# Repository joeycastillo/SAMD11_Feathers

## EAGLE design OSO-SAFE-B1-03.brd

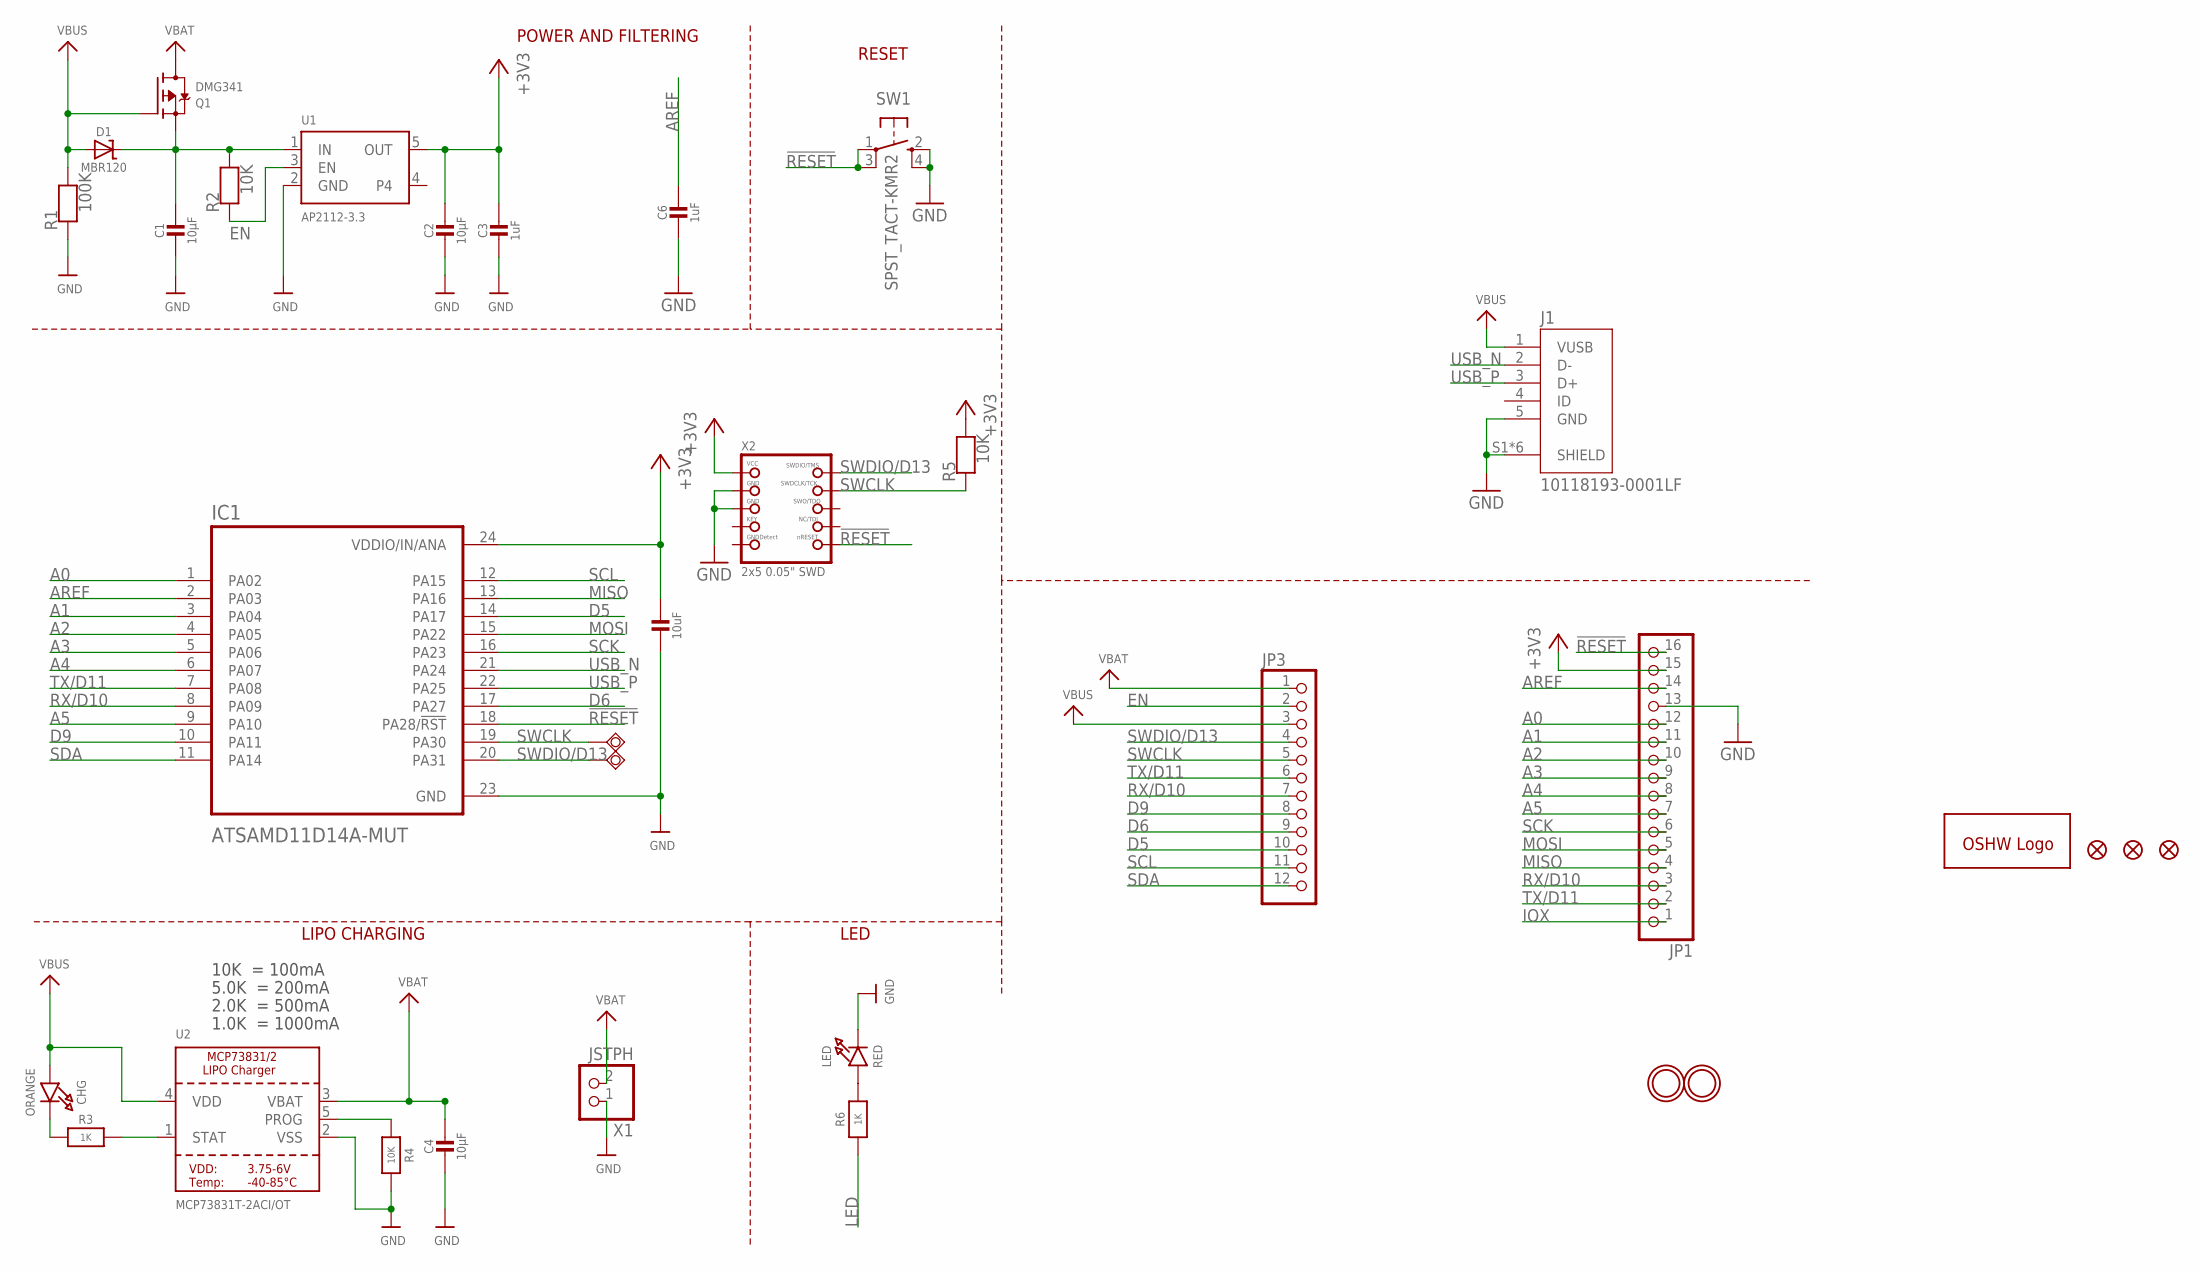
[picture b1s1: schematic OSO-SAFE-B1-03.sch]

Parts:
C1, C2, C4: 10µF; 0805-NO
C3, C6: 1uF; 0805-NO
C5: 10uF; 0805-NO
CHG: ORANGE; CHIPLED_0805_NOOUTLINE
D1: MBR120; SOD-123
FID1, FID3, FID4: FIDUCIAL_1MM
GOLD_ORB_SM1: OSHWLOGOLOGO5MM; OSHW_5MM
IC1: ATSAMD11D14A-MUT; QFN50P400X400X90-25N
J1: 10118193-0001LF; FCI_10118193-0001LF
JP1: HEADER-1X16_MIN; 1X16_ROUND_MIN
JP3: HEADER-1X12_MIN; 1X12_ROUND_MIN
LED: RED; CHIPLED_0805_NOOUTLINE
Q1: DMG341; SOT23-R
R1: 100K; 0805-NO
R2, R4, R5: 10K; 0805-NO
R3, R6: 1K; 0805-NO
SW1: SPST_TACT-KMR2; KMR2
SWCLK: TPSQTP20R; TP20R
SWDIO: TPSQTP20R; TP20R
U1: AP2112-3.3; SOT23-5
U2: MCP73831T-2ACI/OT; SOT23-5
U$31, U$32: MOUNTINGHOLE2.5; MOUNTINGHOLE_2.5_PLATED
X1: JSTPH; JSTPH2
X2: 2x5 0.05" SWD; 2X05_1.27MM_BOX_POSTS

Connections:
!RESET: IC1.18 (PA28/!RST), JP1.16, SW1.1, SW1.3 (P1), X2.10 (NRESET)
+3V3: C2.1, C3.1, C5.1, IC1.24 (VDDIO/IN/ANA), JP1.15, R5.2, U1.5 (OUT), X2.1 (VCC)
A0: IC1.1 (PA02), JP1.12
A1: IC1.3 (PA04), JP1.11
A2: IC1.4 (PA05), JP1.10
A3: IC1.5 (PA06), JP1.9
A4: IC1.6 (PA07), JP1.8
A5: IC1.9 (PA10), JP1.7
AREF: C6.1, IC1.2 (PA03), JP1.14
CHG: CHG.C, R3.1
D5: IC1.14 (PA17), JP3.10
D6: IC1.17 (PA27), JP3.9
D9: IC1.10 (PA11), JP3.8
EN: JP3.2, R2.1, U1.3 (EN)
GND: C1.2, C2.2, C3.2, C4.2, C5.2, C6.2, IC1.23 (GND), J1.5 (GND), J1.S1 (SHIELD), J1.S2 (SHIELD), J1.S3 (SHIELD), J1.S4 (SHIELD), J1.S5 (SHIELD), J1.S6 (SHIELD), JP1.13, LED.C, R1.1, R4.2, SW1.2 (S), SW1.4 (S1), U1.2 (GND), U2.2 (VSS), X1.1, X2.3 (GND), X2.5 (GND)
IOX: JP1.1
LED: R6.1
MISO: IC1.13 (PA16), JP1.4
MOSI: IC1.15 (PA22), JP1.5
unnamed: LED.A, R6.2
PROG: R4.1, U2.5 (PROG)
RX/D10: IC1.8 (PA09), JP1.3, JP3.7
SCK: IC1.16 (PA23), JP1.6
SCL: IC1.12 (PA15), JP3.11
SDA: IC1.11 (PA14), JP3.12
STAT: R3.2, U2.1 (STAT)
SWCLK: IC1.19 (PA30), JP3.5, R5.1, SWCLK.TP, X2.4 (SWDCLK)
SWDIO/D13: IC1.20 (PA31), JP3.4, SWDIO.TP, X2.2 (SWDIO)
TX/D11: IC1.7 (PA08), JP1.2, JP3.6
USB_N: IC1.21 (PA24), J1.2 (D-)
USB_P: IC1.22 (PA25), J1.3 (D+)
VBAT: C4.1, JP3.1, Q1.3 (D), U2.3 (VBAT), X1.2
VBUS: CHG.A, D1.A, J1.1 (VUSB), JP3.3, Q1.1 (G), R1.2, U2.4 (VDD)
VHI: C1.1, D1.C, Q1.2 (S), R2.2, U1.1 (IN)

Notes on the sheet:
LIPO CHARGING
LED
RESET
POWER AND FILTERING
10K = 100mA
5.0K = 200mA
2.0K = 500mA
1.0K = 1000mA

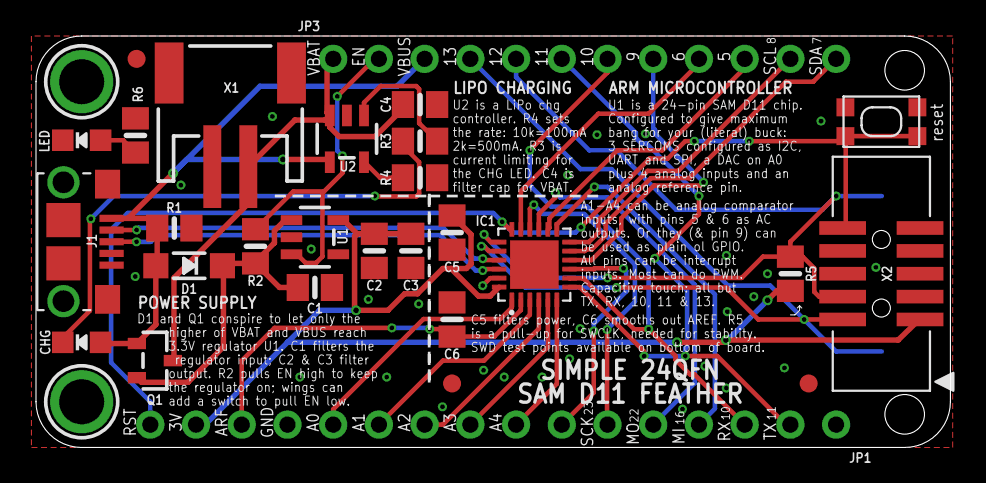
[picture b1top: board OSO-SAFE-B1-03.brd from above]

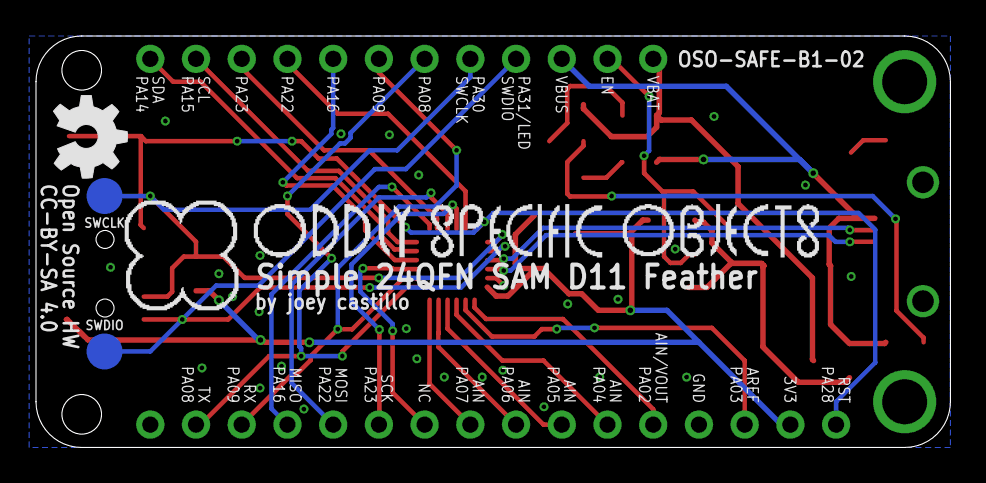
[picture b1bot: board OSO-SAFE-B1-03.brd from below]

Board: 2 copper layers, 50.8 x 22.9 mm, 36 parts (6 on the bottom side), 32 nets.

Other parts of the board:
U$2: OSO_BEAR; OSO_BEAR_750MIL
U$3: OSO_GRAPHIC
U$5: OSO_TEXTOSO_TEXT_ONELINE_125MIL; OSO_ONELINE_125MIL

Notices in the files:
OSO-SAFE-B1-03.brd:
CC-BY-SA 4.0
parts and their libraries:
microbuilder: This work is placed in the public domain, and may be freely used for commercial and non-commercial work with the following conditions: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
